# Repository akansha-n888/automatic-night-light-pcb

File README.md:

# automatic-night-light-pcb
Automatic night light PCB implemented in KiCAD

## Table of contents
* [Motivation](#motivation)
* [Software](#software)
* [Status](#status)
* [Credits](#credits)
* [Contact](#contact)

## Motivation
I grew out of using night lights; my niece on the other hand loves them. I decided that I would buy her one but I didn't like too many of the designs. So I figured that I make my own (or at least try). The first step of my design process starts with a PCB design of a simple night light circuit (available in the Schematic Editor document).

## Software
[KiCAD v 6.0](https://www.kicad.org/)

## Status
Project is: _finished_

## Credits
[KiCAD Like A Pro](https://www.elektor.com/kicad-like-a-pro)

## Contact
Created by [@akansha-n888](https://www.linkedin.com/in/akansha-nagar/) - feel free to contact me!

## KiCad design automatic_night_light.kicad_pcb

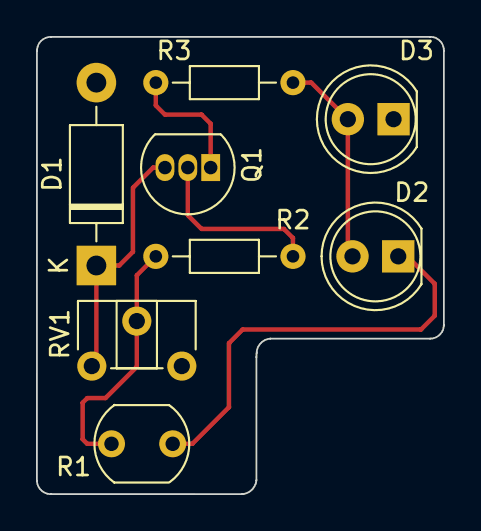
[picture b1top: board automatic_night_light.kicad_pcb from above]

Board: 2 copper layers, 22.6 x 25.4 mm, 8 parts (0 on the bottom side), 6 nets.

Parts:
D1: 1N4001; D_DO-41_SOD81_P10.16mm_Horizontal
D2, D3: LED; LED_D5.0mm
Q1: 2N3904; TO-92_Inline
R1: 1 M; R_LDR_5.1x4.3mm_P3.4mm_Vertical
R2: 22k; R_Axial_DIN0204_L3.6mm_D1.6mm_P7.62mm_Horizontal
R3: 470; R_Axial_DIN0204_L3.6mm_D1.6mm_P7.62mm_Horizontal
RV1: 100k; Potentiometer_ACP_CA6-H2,5_Horizontal

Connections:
GND: D2.1 (K), D3.1 (K), R1.2
unnamed: D1.1 (K), Q1.3 (C), RV1.1
unnamed: D2.2 (A), D3.2 (A), R3.2
unnamed: Q1.1 (E), R3.1
unnamed: Q1.2 (B), R2.2
unnamed: R1.1, R2.1, RV1.2

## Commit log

2022-01-11 add all project files
2022-01-11 Update README.md
    Add readme content
